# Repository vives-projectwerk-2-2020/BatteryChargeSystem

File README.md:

# Battery charge system

## Project description

This project is under the MIT license, view it here [MIT License](license.md)

The concept of the this system is to charge some batteries with a solar panel. To supply the whole system.

## Explanation of my roadmap

I first started with the development boards for charging 1 battery with a solar panel. I had 3 boards for use. So I picked the right one. The Adafruit pcb was very interesting for me. And like we all know a Li- Ion battery must be protected when it's fully charged.
After testing everything on the dev pcb's I started designing my own PCB. I used the Eagle software because we're used to it. It wasn't difficult to find the schematics of the dev PCBs. I used those schematics for my base to draw my own PCB.

The duration test of the pcb went very well. I applied a Arduino Uno and a resistor, so i could test if the pcb works fine. There was a current of 50mA through the resistor. If the panel was all day and night outside, one battery was enough. but when the setup wasn't outside, one battery is enough for 2 days. But we need to cover 2 weeks. But this gave me not a correct view of the situation, because we work with sleep modes. And now i have a constant consumption of 50mA. 

The next step was to draw the final schematic of the PCB. Wich is now half the size of the prototype. We made sure the pcb fits in the box we need to use. In this box sit the LoRaWAN antenna and the main pcb with the Nucleo and the batteries too.

## Problems

I hadn't any problems with the PCB draw. Only needed some research for the GND polygoon.

The first problem that came in the game was the Covid-19 outbreak. No more lessons, no more contact with other students. So it wasn't easy to trade the components between some students.

The second problem was that the pcb got down after 3 minutes. When there was no battery attached to the pcb the system worked fine. But once attached, after three minutes, the PCB shuts down.
I did some debugging. The problem was some duplicate functionality. The main IC thought that there was a fully charged battery attached. The MCP 73871 haves all functionality build in that is necessary. So I scrached a wire away so the other ICs (LC05111CMT and MCP73833). The 2 MCP's have the same functionality.
So now the PCB works fine and I could reduce the needed space on the PCB to a minimum.

## Resources

I used the datasheet of the MCP73871 for debugging my PCB. The other documentation was found on the internet. Mostly used for designing my own PCB.

## Battery Charge System

### Description

This panel provide a charge system for charing the batteries via a solar cell.
It seems to be very easy to make this, but actually there comes a lot to play
in the game.
You'll read here how I made this PCB.

#### Develop boards

I first started with some development boards. These PCB's are for sell on the web.
I got 3 boards, so I need to find out witch one was the best for our project.
In this table you'll see the difference between those development boards.

|Feature|Solar Charge Shield V2.2|Adafruit MCP73871|Sparkfun LiPo USB charger|
| -----------------|:------:|:-----:|:-------:|
| **Output disconect** | X  |    |    |
| **Short circuit protection** | X  | X   |   |
| **3W output power when connecting battery** | X    |   | X    |
| **Continious charge current**| X  | X | x  |
| **Battery status indication** | X   | X    |   |
| **Micro USB connection** | X   | X    | X    |
| **Load sharing** |  | X   |    |
| **Temperature monitoring**  |  | X    | X   |
| **Possible to add extra leds** |  | X   |  |
| **Lithium - Polymer batteries** |    | X   | X   |
| **Lithium - Ion batteries** | X   | X   | X   |

I worked together with my classmate Niels to find out with PCB was the best.
We came to a conclusion that the Adafruit board was the best for us.
So the next step was to find oud how it works and how we need to setup the prototype.

##### More information about the development board

##### Specifications

* 3.7V/4.2V Lithium Ion or Lithium Polymer battery charger
* Charge with 5-6V DC, USB or 6V solar panel!
* Automatic charging current tracking for high efficiency use of any wattage
solar panel
* Use any 6V solar panel
* Three color indicator LEDs - Power good, Charging and Done
* Low Battery Indicator (fixed at 3.1V) with LED output on (labeled CHRG)
* Set for 500mA max charge rate, can be adjusted from 50mA up to 1A by soldering
in a resistor
* Will always draw the most current possible from a solar cell- up to the max
charge rate!
* Smart load sharing automatically uses the input power when available, to keep
battery from constantly charging/discharging
* Temperature monitoring of battery by soldering in a 10K NTC thermistor
[thermistor](http://adafru.it/372) (not included) - suggested for outdoor projects
where the battery may get hot (50°C) or cold (0°C).

##### Indicator led's

* The red PWR LED indicates that there is good power connected to the charger.
If this LED is not lit, something is wrong with the power supply
* The orange CHRG LED indicates current charging status. When this LED is lit,
the charger is working to charge up a battery! It also acts as a low battery
indicator (fixed at 3.1V) when no power is connected. So, if you don't have
USB/Solar wired up, when the battery voltage drops below 3.1V, the orange LED
will come on.
* The green DONE LED is pretty easy to understand as well - when it's lit the
battery is charged up! Very handy for when you want to know that everything is done.

##### Extra features

* Load Sharing
* Temperature monitoring
* Adjusting the max charge current
* Adding external LEDs

This was quite easy.
In the picture below you'll see how is set this configuration up.

In the first pic it's the concept of the configuration.

This system was well tested, so I did some measurements  to see how good it works.
You can see some pictures of the measurements below

##### Charge voltage

As we can see, the batteries are supplied with a voltage of 4.3V. A Li-Ion battery
of 3.7V loads until it reaches 4.2V. You can see in the picture of the battery
voltage, that he isn't charged fully. So The charge current is maximum.

##### Charge current

When the battery voltage raises, the charge current will go down. When 4.2V is
reached, the charge current is 0A.
So the current you see on the display, is near maximum.

##### Battery voltage

The battery voltage is not high, the voltage will go to 4.2V.

##### solar panel voltage

The solar panel provides a voltage of near 7V. This is quite high! In my own
PCB I'll need to protect my main IC from this high voltage.

### Our own design

#### Description of my own design

I used the development boards to look for some inspiration, so I could (easily)
make my own design. I started with a prototype, and I'll explain how this works.

#### Schematic

##### Description of the schematic

This is the prototype schematic with actually some bugs in it.
The first IC (MCP73871) manages the battery. This was the same IC of the
development board. He'll keep track on the charge current and voltage. When the
battery is charged, the charge current will be 0 because this IC will drop it down.
There is also a possibility to get some information via the PG, STAT1, STAT2 pins.
These aren't provided here, but in the final PCB it does. This IC takes the
voltage from the solar panel and have's an output of 4.3V.

The second IC is a battery management IC too, this will cause problems. You'll
see in the final PCB that this IC is deleted. In first place I thought that it
was necessary to provide a protection circuit for the battery. But the MCP73871
haves already this functionality. So I will discuss my problems later in this
document, and will explain there what went wrong.

The other components are some interfacing for these IC's.

#### Board

##### Description of the board

The next step was to draw the board. This is quite easy. The first picture is
the schematic witout polygon, the second one is the PCB with polygon. We let
these PCB's made in Japan. Via [JLCPCB](http://JLCPCB.com). Then we bought our
components by Farnell for fast shipping. When we got all components and boards,
we could start soldering. Me and my colleagues are used to solder, so this
wasn't any problem for us.

In this pic you'll see the unsoldered and soldered PCB

#### Description of the final design

You can find here the link to the GitHub repo of the schematic, board and partlist.
[GitHub repo final design](https://github.com/vives-projectwerk-2-2020/FinalSolarChargeSystem)

#### Final Schematic

##### Description of the final schematic

As you can see here, the other IC's are removed. This because they have the same
functionality as the MCP73871. I placed a voltage regulator before the IC, this
is because you can have a max voltage of 6V on the IC, and the solar panel
provides 6+V.
Here I brought the STAT1, STAT2 and PG pins outside, so we can manage the battery
on the Nucleo.
This PCB will fit on the main PCB (See Niels his documents).

#### Final Board

##### Description of the final Board

There is not so much to tell about it, here to, just draw the wires.
We couldn't order these PCB's because of the COVID-19 pandemic.

### Tests

When we had the prototype PCB, we soldered them, and then we need to test if they
really work.

When I tested the PCB without a battery connected, the charge voltage was 4.2V.
This was really good, that worked. But when I attached a battery, the system
falls down after 2 minutes. So is started looking for the problem. And as you
could see, there is a difference between the prototype PCB and the final PCB.
1 IC in stead of 3. This was because the MCP73871 have same functionality of all
those other IC's. So I don't need them. What was the source of the problem? Well,
the MCP73871 checked the battery status, but he actually checked the MCP83833
and this IC wasn't a battery, so the MCP73871 shuts down because he thought that
te battery was fully charged.
When scratching away the wire tot the MCP83833, the PCB worked like it need to be!

After this, is started a duration test. I made a setup with a Arduino UNO to
have a current taken away from the battery.
The charge PCB was still connected to the batteries.
The setup have been outside for 3 - 4 weeks, day and night.
In the picture below, you'll see the setup I made.

I went daily for a measurement of the PCB. I measured the voltage of the solar
panel, IC input, IC output, battery voltage and charge current.
|Measurement    | Value         |
|---------------|---------------|
|Solar panel    |6,8V           |
|IC input       |5V             |
|IC output      |4,2V           |
|Battery voltage|3V - 4.2V      |
|charge current |0mA - 100mA    |

The charge current depends on the weather. When it is a nice day, you'll reach
higher current measurements. The charge current depends on the battery voltage
too. When the battery voltage reaches 4.2V, the current will drop town to 0.

How I did these measurements, can be found in my Youtube video.

### Links

* [MCP73871 datasheet](http://adafru.it/aMO)
* [Fritzing object in Adafruit Fritzing library](http://adafru.it/aP3)
* [EagleCAD Board / Layout & Schematic files on Github](http://adafru.it/aMP)

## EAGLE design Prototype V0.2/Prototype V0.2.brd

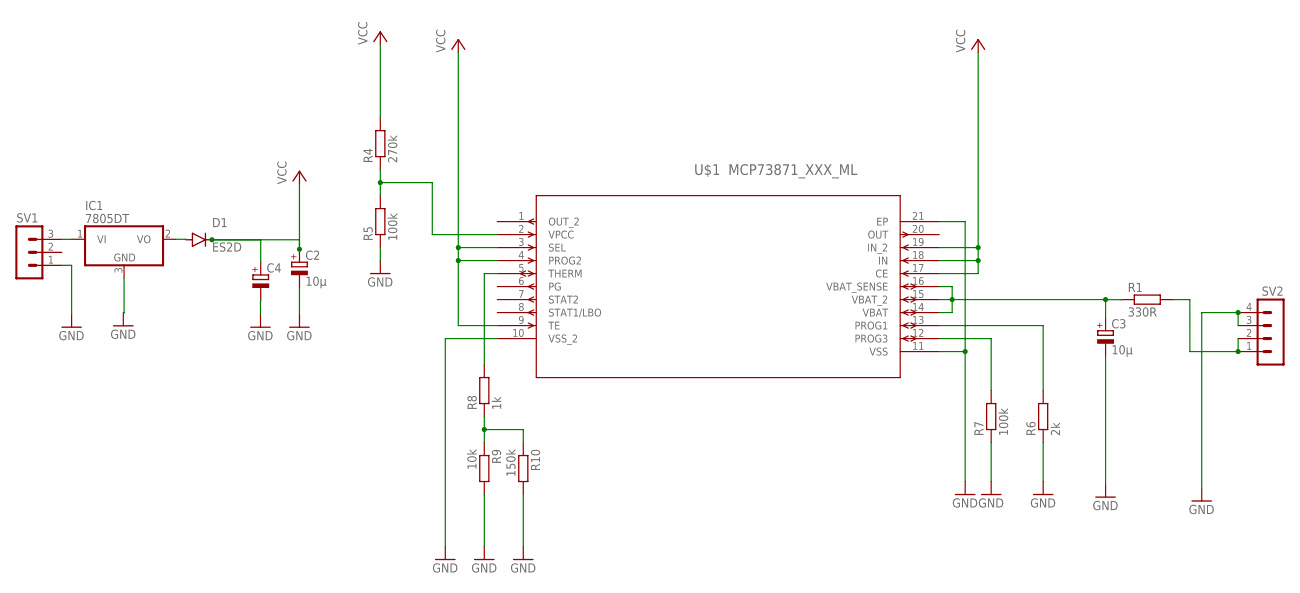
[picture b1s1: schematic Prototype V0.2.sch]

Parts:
C2, C3: 10µ; 153CLV-0505
C4: CPOL-EUE2.5-6; E2,5-6
D1: ES2D; SMB
IC1: 7805DT; TO252
R1: 330R; R0603
R4: 270k; R0603
R5, R7: 100k; R0603
R6: 2k; R0603
R8: 1k; R0603
R9: 10k; R0603
R10: 150k; R0603
SV1: MA03-1
SV2: MA04-1
U$1: MCP73871_XXX_ML; QFN20_4X4MC

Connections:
GND: C2.-, C3.-, C4.-, IC1.3 (GND), R5.1, R6.1, R7.1, R9.2, R10.2, SV1.1, SV2.3, SV2.4, U$1.10 (VSS_2), U$1.11 (VSS), U$1.21 (EP)
unnamed: R1.2, SV2.1, SV2.2
unnamed: IC1.1 (VI), SV1.3
unnamed: D1.A, IC1.2 (VO)
unnamed: R4.1, R5.2, U$1.2 (VPCC)
unnamed: R7.2, U$1.12 (PROG3)
unnamed: R8.1, R9.1, R10.1
unnamed: R6.2, U$1.13 (PROG1)
unnamed: R8.2, U$1.5 (THERM)
VCC: C2.+, C4.+, D1.C, R4.2, U$1.3 (SEL), U$1.4 (PROG2), U$1.9 (TE), U$1.17 (CE), U$1.18 (IN), U$1.19 (IN_2)
VIN: C3.+, U$1.14 (VBAT), U$1.15 (VBAT_2), U$1.16 (VBAT_SENSE)

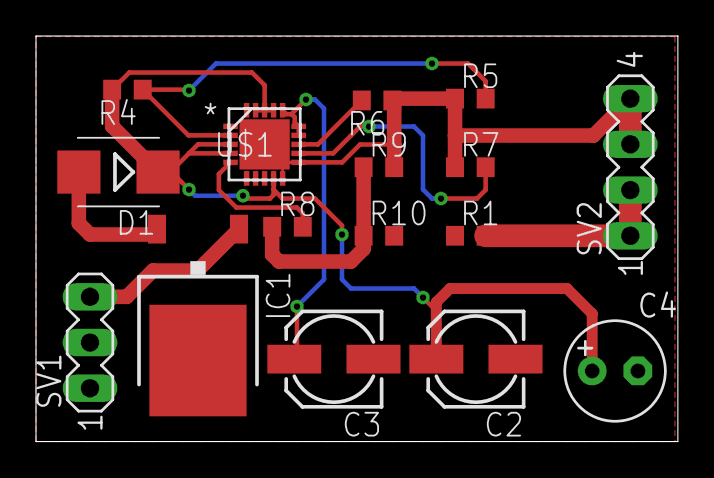
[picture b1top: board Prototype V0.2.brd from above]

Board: 2 copper layers, 35.7 x 22.5 mm, 16 parts (0 on the bottom side), 11 nets.

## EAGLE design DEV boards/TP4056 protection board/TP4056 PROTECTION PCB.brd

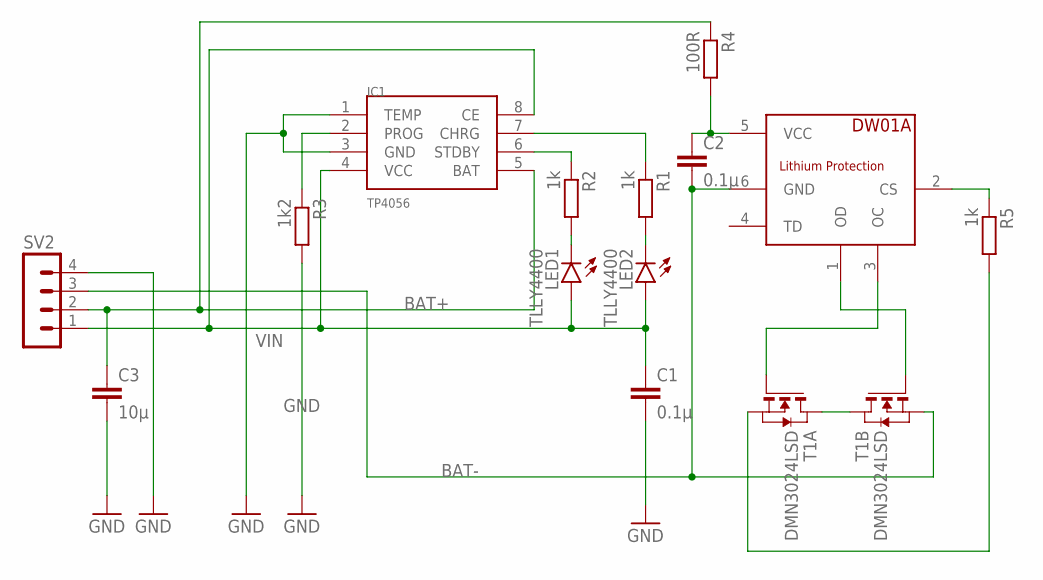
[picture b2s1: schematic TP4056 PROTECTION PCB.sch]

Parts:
C1, C2: 0.1µ; C1206
C3: 10µ; C1206
IC1: TP4056; SOP-8
LED1, LED2: TLLY4400; LED3MM
R1, R2, R5: 1k; R1206W
R3: 1k2; R1206W
R4: 100R; R1206W
SV2: MA04-1
T1: DMN3024LSD; TSSOP-8
U$1: DW01A; SOT23-6

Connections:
BAT+: C3.1, IC1.5 (BAT), R4.1, SV2.2
BAT-: C2.2, SV2.3, T1.6 (S), T1.7 (S), U$1.6 (GND)
GND: C1.2, C3.2, IC1.1 (TEMP), IC1.3 (GND), R3.2, SV2.4
unnamed: IC1.6 (STDBY), R2.1
unnamed: IC1.7 (CHRG), R1.1
unnamed: LED2.K (C), R1.2
unnamed: LED1.K (C), R2.2
unnamed: C2.1, R4.2, U$1.5 (VCC)
unnamed: R5.1, U$1.2 (CS)
unnamed: IC1.2 (PROG), R3.1
unnamed: T1.4 (G), U$1.3 (OC)
unnamed: T1.5 (G), U$1.1 (OD)
unnamed: T1.1 (D), T1.8 (D)
unnamed: R5.2, T1.2 (S), T1.3 (S)
VIN: C1.1, IC1.4 (VCC), IC1.8 (CE), LED1.A, LED2.A, SV2.1

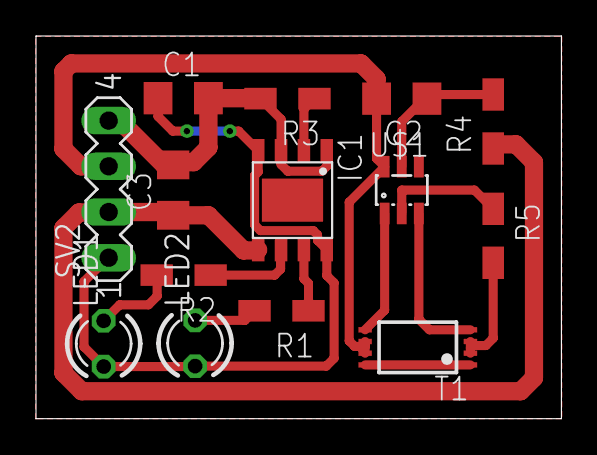
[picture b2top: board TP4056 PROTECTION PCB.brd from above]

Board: 2 copper layers, 29.2 x 21.3 mm, 14 parts (0 on the bottom side), 15 nets.

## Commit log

2020-04-16 adding the full project into the git repo
2020-05-22 adding the documentation here too
2020-05-22 adding the license file
